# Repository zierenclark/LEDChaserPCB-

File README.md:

# LEDChaserPCB-
Goal: Build LED chaser circuit PCB from online LEDchaser Schamtic on circuitdigest.com

Schematic from: https://circuitdigest.com/electronic-circuits/led-chaser-circuit

The circuit is designed to Power 10 LEDs in an on-and-off sequence similar to decorative lights. This circuit uses a 555 IC timer to generate a high and low signal at different frequencies according to the resistance of a potentiometer. This signal is then inputted into a 4017IC that changes in stage with each cycle of the 555 IC timer. This circuit uses another LED just to determine the frequency of the cycles that the 555 IC is outputting. 

Equations for the 555 Timer:

High Output Signal: T1 = 0.693(R1+VR)C1  -----> VR = Variable Resistor(Potentiometer)

Low Output Signal: T2 = 0.693(R2)C1

Total Period: T = T1 + T2 = 0.693(R1+2VR)C1

Frequency Oscicillation: F = 1/T, F = 1.44/(R1+2VR)C1

Equations are from the online schematic.

Started by initially building the circuit on the breadboard to ensure all components worked properly and the schematic was correctly designed for the initial purpose.  Had to change all 150 Ohm resistors to 220 Ohm due to component availability. 

Once I confirmed the schematic was working properly, I began building it in Eagle PCB software. Going from schematic to PCB was particularly difficult since the stages of the 4017IC were not in order by the next stage due to the necessary design of the integrated circuit.

After printing the PCB on the LPKF S104 CNC mill, I assembled and soldered the circuit using the components from the breadboard prototype. 

Initially, the circuit was not receiving power due to a faulty positive wire I had soldered originally. After replacing the wire, the circuit nearly worked correctly except for an LED not flashing during the fifth stage which was due to a faulty connection during soldering.

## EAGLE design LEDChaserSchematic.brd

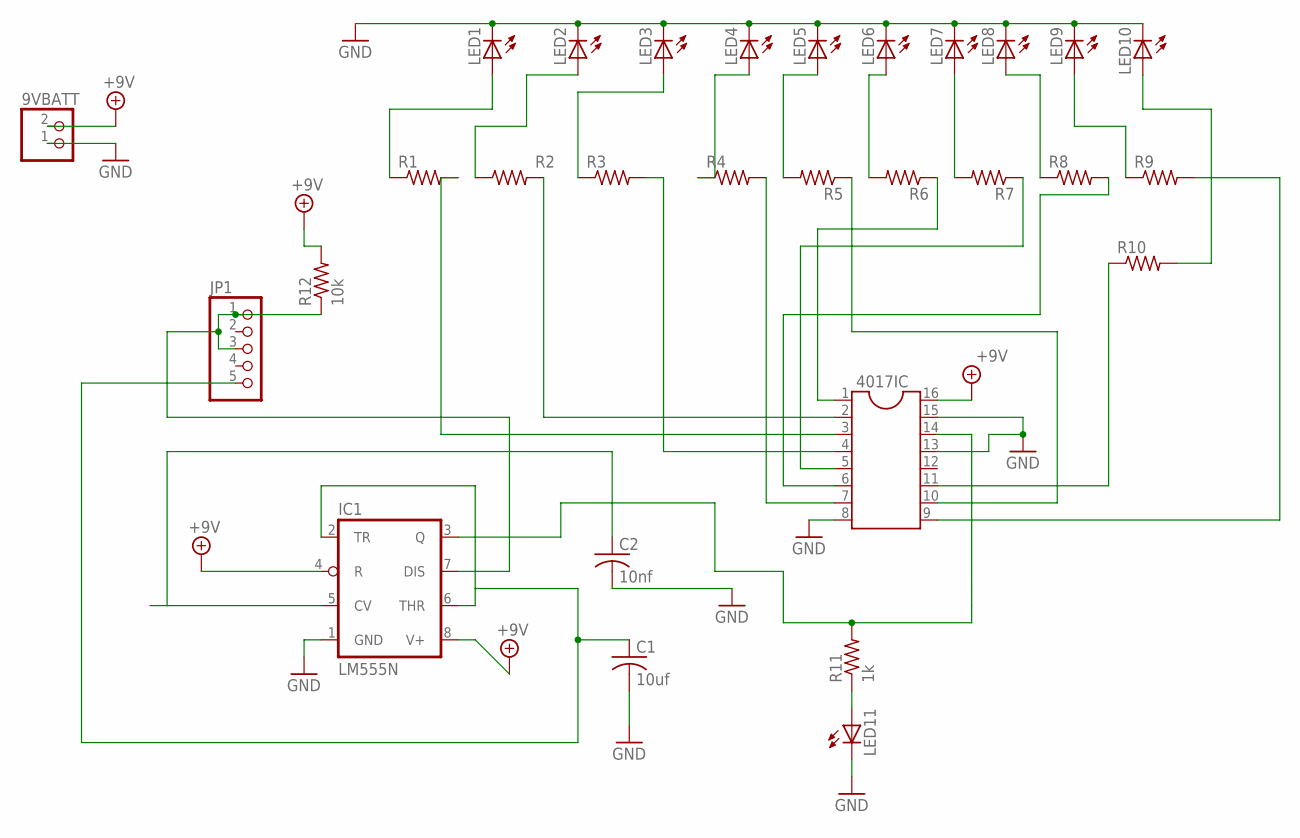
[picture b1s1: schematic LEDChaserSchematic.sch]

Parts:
9VBATT: JST_2PIN-THM; JST-PH-2-THM
4017IC: DIL16
C1: 10uf; C025-030X050
C2: 10nf; C025-030X050
IC1: LM555N; DIL08-ROUND
JP1: PINHD-1X5; 1X05
LED1, LED2, LED3, LED4, LED5, LED6, LED7, LED8, LED9, LED10, LED11: LED5MM
R1, R2, R3, R4, R5, R6, R7, R8, R9, R10: R-US_0204/5; 0204/5
R11: 1k; 0204/5
R12: 10k; 0204/5

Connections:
+9V: 9VBATT.2 (1), 4017IC.16, IC1.4 (R), IC1.8 (V+), R12.2
GND: 9VBATT.1 (2), 4017IC.8, 4017IC.13, 4017IC.15, C1.2, C2.2, IC1.1 (GND), LED1.K (C), LED2.K (C), LED3.K (C), LED4.K (C), LED5.K (C), LED6.K (C), LED7.K (C), LED8.K (C), LED9.K (C), LED10.K (C), LED11.K (C)
unnamed: LED1.A, R1.1
unnamed: LED2.A, R2.1
unnamed: LED3.A, R3.1
unnamed: LED4.A, R4.1
unnamed: LED5.A, R5.2
unnamed: LED6.A, R6.2
unnamed: LED7.A, R7.2
unnamed: LED8.A, R8.1
unnamed: LED9.A, R9.1
unnamed: LED10.A, R10.2
unnamed: 4017IC.3, R1.2
unnamed: 4017IC.2, R2.2
unnamed: 4017IC.4, R3.2
unnamed: 4017IC.7, R4.2
unnamed: 4017IC.10, R5.1
unnamed: 4017IC.1, R6.1
unnamed: 4017IC.5, R7.1
unnamed: 4017IC.6, R8.2
unnamed: 4017IC.9, R9.2
unnamed: 4017IC.11, R10.1
unnamed: C1.1, IC1.2 (TR), IC1.6 (THR), JP1.5
unnamed: C2.1, IC1.5 (CV)
unnamed: 4017IC.14, IC1.3 (Q), R11.2
unnamed: LED11.A, R11.1
unnamed: IC1.7 (DIS), JP1.1, JP1.3, R12.1

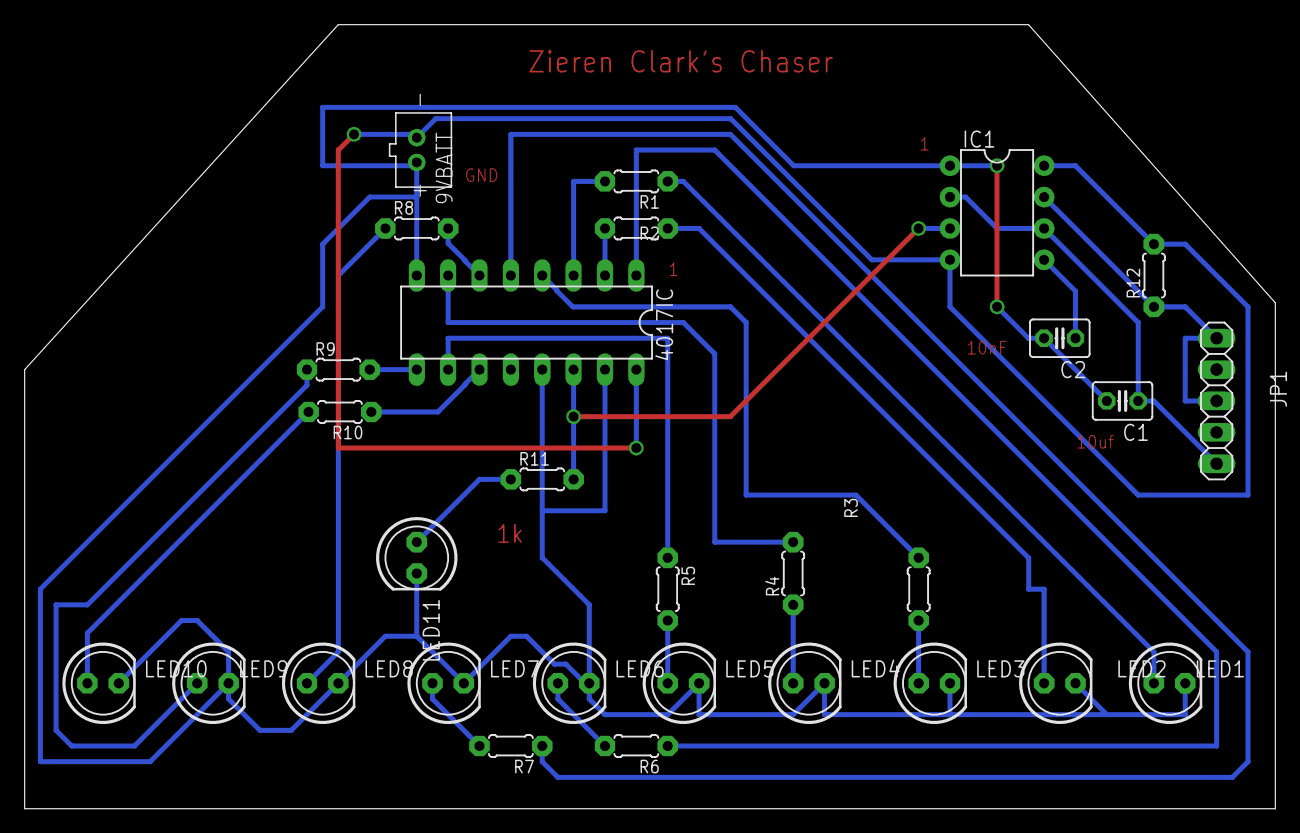
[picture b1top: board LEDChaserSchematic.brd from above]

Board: 2 copper layers, 101.3 x 63.5 mm, 29 parts (0 on the bottom side), 27 nets.
